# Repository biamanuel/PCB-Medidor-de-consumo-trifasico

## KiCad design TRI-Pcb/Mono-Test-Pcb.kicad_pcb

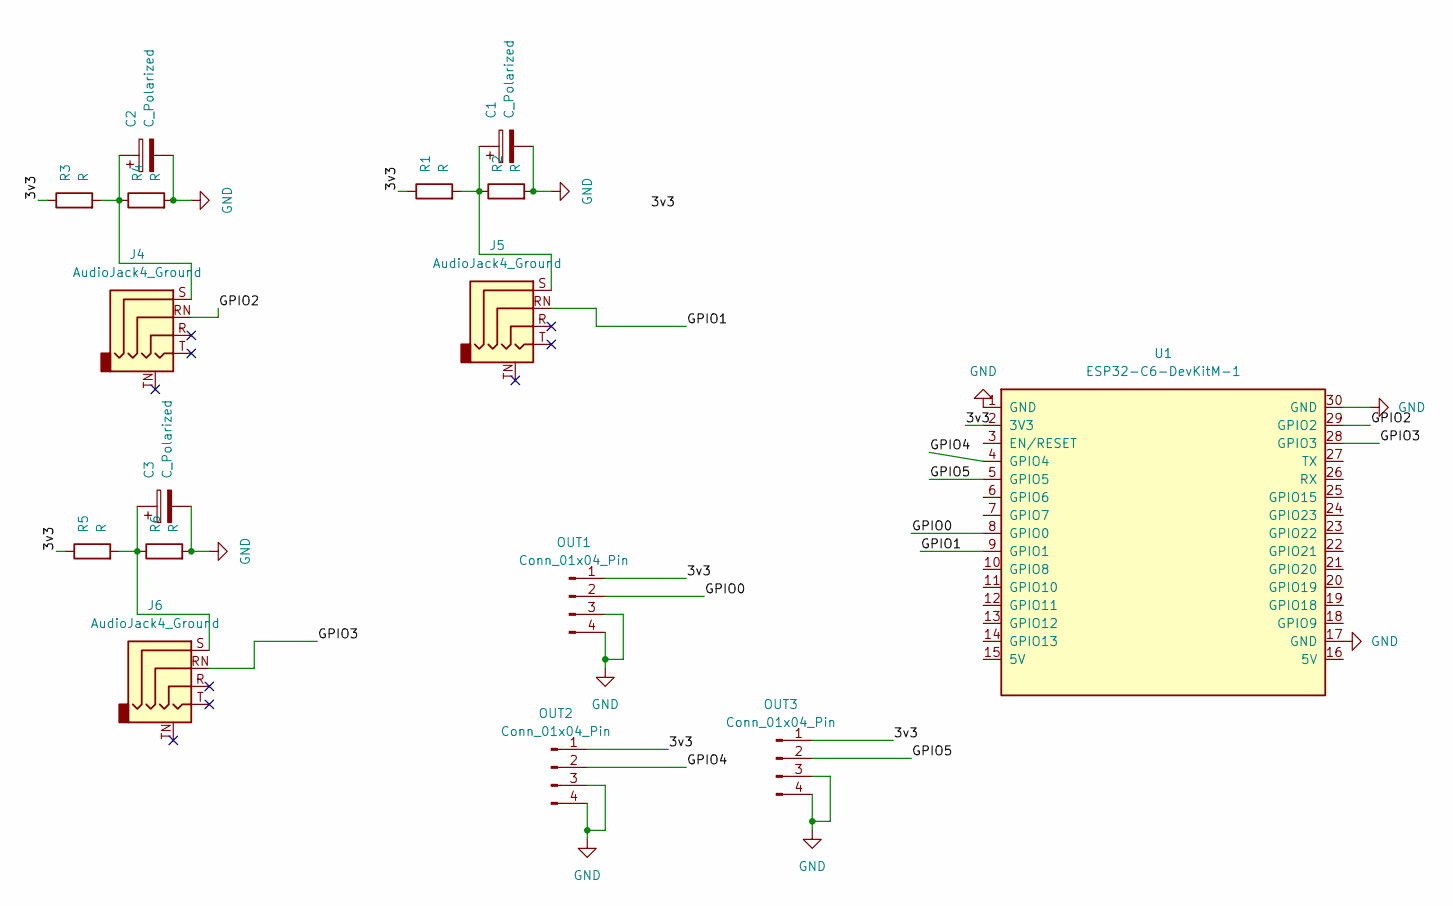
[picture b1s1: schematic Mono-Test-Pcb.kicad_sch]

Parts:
C1, C2, C3: C_Polarized; CP_Radial_D5.0mm_P2.50mm
J4, J5, J6: AudioJack4_Ground; Jack_3.5mm_CUI_SJ1-3515N_Horizontal
OUT1, OUT2, OUT3: Conn_01x04_Pin; FanPinHeader_1x04_P2.54mm_Vertical
R1, R2, R3, R4, R5, R6: R; R_Axial_DIN0207_L6.3mm_D2.5mm_P15.24mm_Horizontal
U1: ESP32-C6-DevKitM-1

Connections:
/3v3: OUT1.1, OUT2.1, OUT3.1, R1.1, R3.1, R5.1, U1.2 (3V3)
/GPIO0: OUT1.2, U1.8 (GPIO0)
/GPIO1: J5.RN, U1.9 (GPIO1)
/GPIO2: J4.RN, U1.29 (GPIO2)
/GPIO3: J6.RN, U1.28 (GPIO3)
/GPIO4: OUT2.2, U1.4 (GPIO4)
/GPIO5: OUT3.2, U1.5 (GPIO5)
GND: C1.2, C2.2, C3.2, OUT1.3, OUT1.4, OUT2.3, OUT2.4, OUT3.3, OUT3.4, R2.2, R4.2, R6.2, U1.1 (GND), U1.17 (GND), U1.30 (GND)
unnamed: C1.1, J5.S, R1.2, R2.1
unnamed: C2.1, J4.S, R3.2, R4.1
unnamed: C3.1, J6.S, R5.2, R6.1

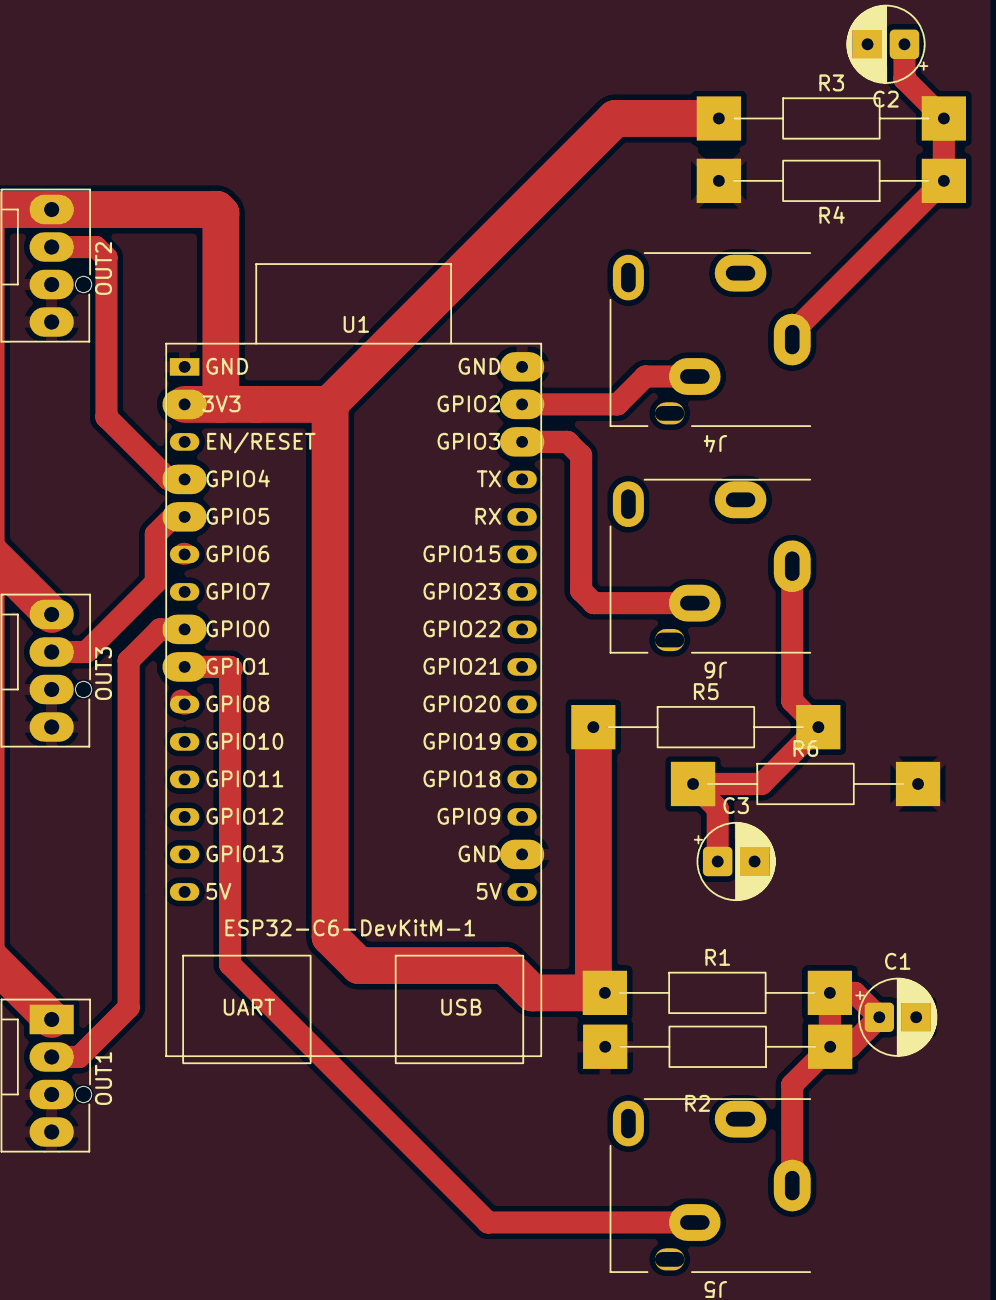
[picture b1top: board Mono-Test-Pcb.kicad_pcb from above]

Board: 2 copper layers, 16 parts (0 on the bottom side), 11 nets.
